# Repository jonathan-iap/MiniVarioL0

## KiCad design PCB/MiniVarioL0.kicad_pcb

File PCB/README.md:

Tool_Kicad-EmptyProject
===============

Empty project for new project based on Kicad

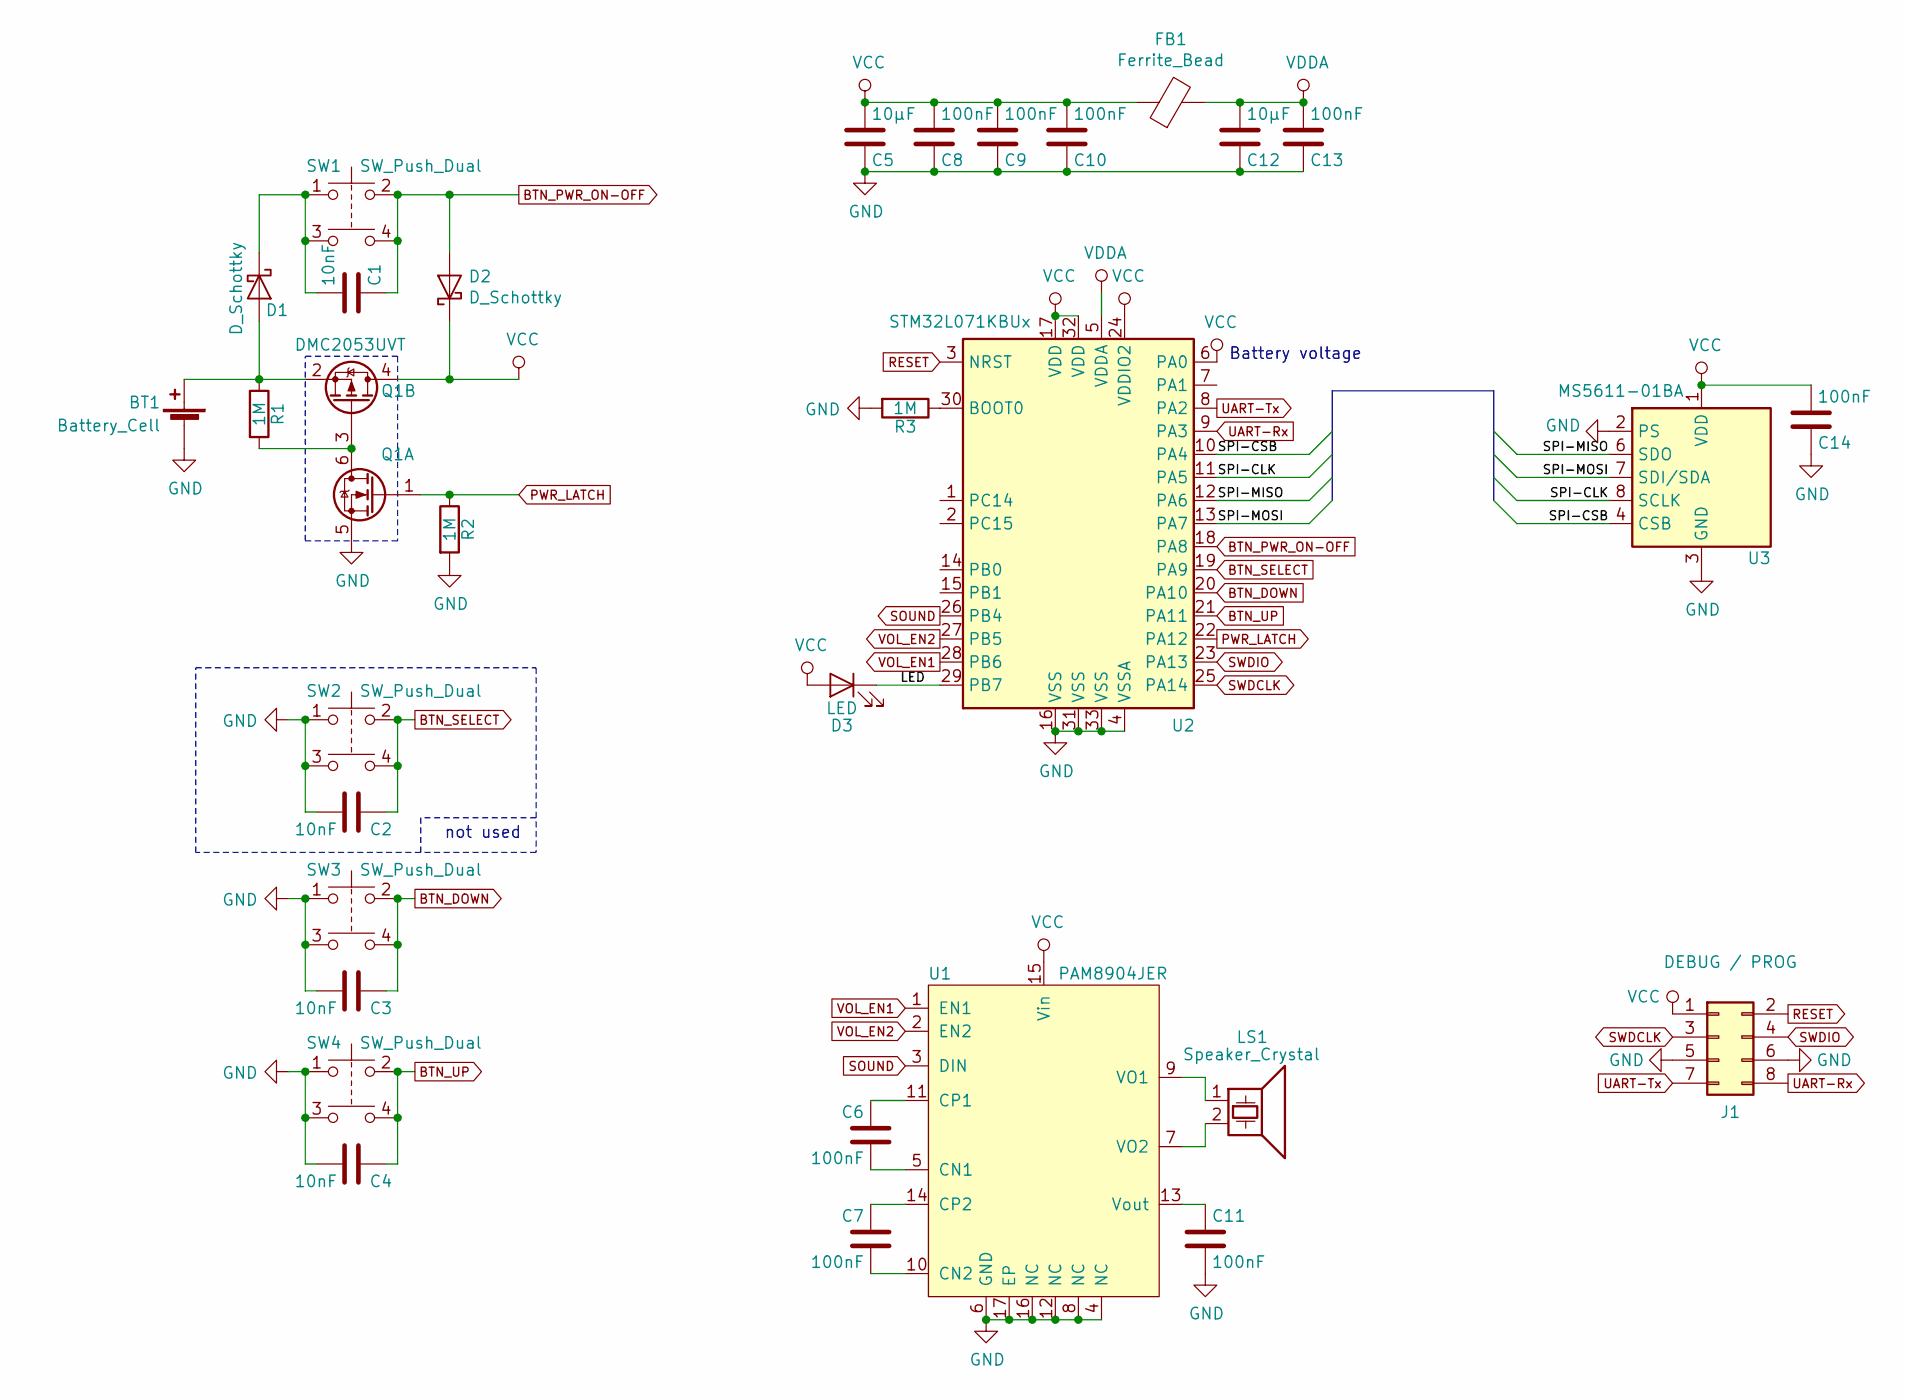
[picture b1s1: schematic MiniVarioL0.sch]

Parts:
BT1: Battery_Cell; CellCoin_BK-912
C1, C2, C3, C4: 10nF; C_0402
C5, C12: 10µF; C_0603
C6, C7, C8, C9, C10, C11, C13, C14: 100nF; C_0402
D1, D2: D_Schottky; D_0603
D3: LED; LED_0603
FB1: Ferrite_Bead; L_0603
J1: DEBUG / PROG; Conn_Debug
LS1: Speaker_Crystal; Buzzer_PKLCS1212E
Q1: DMC2053UVT; TSOT-23-6
R1, R2, R3: 1M; R_0402
SW1, SW2, SW3, SW4: SW_Push_Dual; PushButton_KMS233G
U1: PAM8904JER; UQFN-16-1EP_3x3mm_Pitch0.5mm
U2: STM32L071KBUx; QFN-32-1EP_5x5mm_Pitch0.5mm
U3: MS5611-01BA; LGA-8_3x5mm_Pitch1.25mm

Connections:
/LED: D3.1 (K), U2.29 (PB7)
/SPI-CLK: U2.11 (PA5), U3.8 (SCLK)
/SPI-CSB: U2.10 (PA4), U3.4 (CSB), U3.5 (CSB)
/SPI-MISO: U2.12 (PA6), U3.6 (SDO)
/SPI-MOSI: U2.13 (PA7), U3.7 (SDI/SDA)
BTN_DOWN: C3.1, SW3.2, SW3.4, U2.20 (PA10)
BTN_PWR_ON-OFF: C1.1, D2.2 (A), SW1.2, SW1.4, U2.18 (PA8)
BTN_SELECT: C2.1, SW2.2, SW2.4, U2.19 (PA9)
BTN_UP: C4.1, SW4.2, SW4.4, U2.21 (PA11)
GND: BT1.2 (-), C2.2, C3.2, C4.2, C5.1, C8.1, C9.1, C10.1, C11.2, C12.1, C13.1, C14.1, J1.5, J1.6, Q1.5 (S), R2.2, R3.2, SW2.1, SW2.3, SW3.1, SW3.3, SW4.1, SW4.3, U1.4 (NC), U1.6 (GND), U1.8 (NC), U1.12 (NC), U1.16 (NC), U1.17 (EP), U2.4 (VSSA), U2.16 (VSS), U2.31 (VSS), U2.33 (VSS), U3.2 (PS), U3.3 (GND)
unnamed: BT1.1 (+), D1.2 (A), Q1.2 (S), R1.1
unnamed: C1.2, D1.1 (K), SW1.1, SW1.3
unnamed: C6.1, U1.11 (CP1)
unnamed: C6.2, U1.5 (CN1)
unnamed: C7.1, U1.14 (CP2)
unnamed: C7.2, U1.10 (CN2)
unnamed: C11.1, U1.13 (Vout)
unnamed: LS1.1, U1.9 (VO1)
unnamed: LS1.2, U1.7 (VO2)
unnamed: Q1.3 (G), Q1.6 (D), R1.2
unnamed: R3.1, U2.30 (BOOT0)
PWR_LATCH: Q1.1 (G), R2.1, U2.22 (PA12)
RESET: J1.2, U2.3 (NRST)
SOUND: U1.3 (DIN), U2.26 (PB4)
SWDCLK: J1.3, U2.25 (PA14)
SWDIO: J1.4, U2.23 (PA13)
UART-Rx: J1.8, U2.9 (PA3)
UART-Tx: J1.7, U2.8 (PA2)
VCC: C5.2, C8.2, C9.2, C10.2, C14.2, D2.1 (K), D3.2 (A), FB1.1, J1.1, Q1.4 (D), U1.15 (Vin), U2.6 (PA0), U2.17 (VDD), U2.24 (VDDIO2), U2.32 (VDD), U3.1 (VDD)
VDDA: C12.2, C13.2, FB1.2, U2.5 (VDDA)
VOL_EN1: U1.1 (EN1), U2.28 (PB6)
VOL_EN2: U1.2 (EN2), U2.27 (PB5)

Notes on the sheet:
Battery voltage
not used

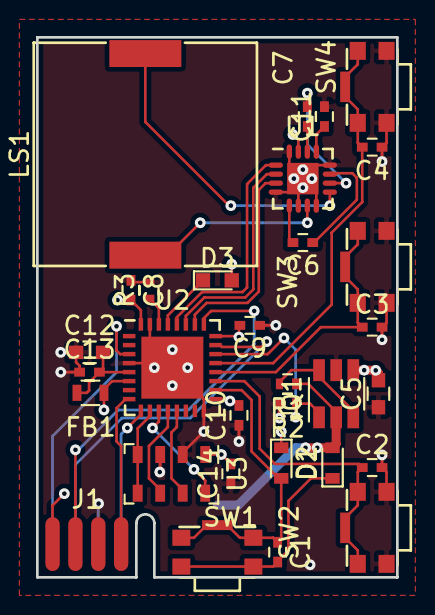
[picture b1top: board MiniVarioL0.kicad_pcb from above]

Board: 4 copper layers, 20.0 x 30.0 mm, 32 parts (1 on the bottom side), 32 nets.

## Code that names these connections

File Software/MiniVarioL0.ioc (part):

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Mcu.Name=STM32L071K(B-Z)Ux
Mcu.Package=UFQFPN32
Mcu.UserName=STM32L071KBUx
PA0.GPIOParameters=GPIO_Label
PA0.GPIO_Label=Vbatt
PA0.Mode=IN0
PA0.Signal=ADC_IN0
PA10.GPIOParameters=GPIO_PuPd,GPIO_Label
PA10.GPIO_Label=BTN_DOWN
PA10.GPIO_PuPd=GPIO_PULLUP
PA10.Signal=GPIO_Input
PA11.GPIOParameters=GPIO_PuPd,GPIO_Label
PA11.GPIO_Label=BTN_UP
PA11.GPIO_PuPd=GPIO_PULLUP
PA11.Signal=GPIO_Input
PA12.GPIOParameters=GPIO_Label
PA12.GPIO_Label=PWR_LATCH
PA12.Signal=GPIO_Output
PA13.Mode=Serial_Wire
PA13.Signal=SYS_SWDIO
PA14.Mode=Serial_Wire
PA14.Signal=SYS_SWCLK
PA2.Mode=Asynchronous
PA2.Signal=LPUART1_TX
PA3.Mode=Asynchronous
PA3.Signal=LPUART1_RX
PA4.GPIOParameters=GPIO_Label
PA4.GPIO_Label=SPI1_CS
PA4.Signal=GPIO_Output
PA5.Mode=Full_Duplex_Master
PA5.Signal=SPI1_SCK
PA6.Mode=Full_Duplex_Master
PA6.Signal=SPI1_MISO
PA7.Mode=Full_Duplex_Master
PA7.Signal=SPI1_MOSI
PA8.GPIOParameters=GPIO_PuPd,GPIO_Label
PA8.GPIO_Label=BTN_PWR_ON-OFF
PA8.GPIO_PuPd=GPIO_PULLDOWN
PA8.Signal=GPIO_Input
PA9.GPIOParameters=GPIO_PuPd,GPIO_Label
PA9.GPIO_Label=BTN_SELECT
PA9.GPIO_PuPd=GPIO_PULLUP
PA9.Signal=GPIO_Input
PB4.Signal=S_TIM3_CH1
PB5.GPIOParameters=GPIO_Label
PB5.GPIO_Label=VOL_EN2
PB5.Signal=GPIO_Output
PB6.GPIOParameters=GPIO_Label
PB6.GPIO_Label=VOL_EN1
PB6.Signal=GPIO_Output
PB7.GPIOParameters=GPIO_Label
PB7.GPIO_Label=LED
PB7.Signal=GPIO_Output
RCC.SYSCLKFreq_VALUE=2097000
board=custom

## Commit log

2019-11-09 hardware v1.0.0 and hardware checking in software
